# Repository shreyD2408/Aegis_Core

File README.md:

# Aegis Core RP2350A 

# Overview 

When I decided to make the Aegis Core, I set out to make a clean, professional looking, all-in-one controller board for high end automated turrets and robotic aiming platforms. Typically, projects of this kind involve a clutter of jumper wires, stacked development boards, and external regulator boards, all of which can be affected by electrical noise and poor connections in high-vibration moments.

I designed Aegis Core to solve these challenges head-on. By integrating everything onto a custom 2-Layer PCB powered by the new RP2350A, Aegis Core handles real-time USB tracking telemetry, high-current low-side N-Channel MOSFET flywheel driver stages, multi-channel precision servo actuation, automated reloading sequences, and system audio feedback, all driven natively from a compact 2S Li-ion battery architecture.

# How It Works: System Architecture

Aegis Core is structured into three primary electrical and computational domains to ensure high performance and zero brownouts under heavy mechanical load.

1. Power Regulation & Destribution
    Input Stage: Power is connected through an XT30 connector (+BATT) directly connected to a bulk filtering electrolytic capacitor where the severe    inductive current transients that occur when the flywheel motors and servos snap into action are absorbed.
  
  Buck Regulation: A high-efficiency, 500kHz synchronous buck converter reduces the battery voltage range of approximately 7.4V nominal/8.4V max to   a strong and clean 5.0V system rail. Input voltage allows for up to 8S batteries to be connected, although it is not    recommend. Input voltage ranges from 6-30V. The input ceramic decoupling capacitors, output bypass capacitors, bootstrap capacitor and soft-start capacitor are carefully chosen low-ESR surface-mount devices to ensure loop stability. 

2. Processing & Core Logic
   The RP2350 microcontroller is located near the center of the board and is supported by the external Winbond SPI Flash memory, and a 3225-package    crystal oscillator with high precision.

   The RP2350A processes incoming USB serial tracking commands from a host computer running computer vision scripts, translating coordinates into
   smooth PWM signals and hardware triggers in real-time.

3. Actuation & Peripherals
   Flywheel Control: Flywheel cages are driven by a pair of high-current brushed motors controlled by a low-side A03400A N-Channel MOSFET high speed
   electronic switch.

   Servos: Three exclusive header channels for accurate PWM output of 50Hz for pan, tilt, and an automatic reload indexing mechanism.

   Audio & Input: An integrated piezo buzzer emits audible telemetry signals (startup melodies, arming tones and firing clicks), and the tactile
   push buttons allow the user with BOOTSEL and RESET buttons.

# Visuals & Layouts

   Schemaitc:

   Board Layout:

   3D Model:

# Wiring & Interconnect Diagram

Because Aegis Core concentrates peripheral connections onto organized onboard headers, external hand-wiring is kept to an absolute minimum:

- XT30 Connector: Main 2S Li-ion battery input
- Flywheel Output Terminals: Screw terminals connected to the drain pins of the A03400A MOSFET low-side drivers.
- Pan Servo Header: 3-pin header (signal to RP2350 GPIO 0, 5V, GND)
- Tilt Servo Header: 3-pin header (signal to RP2350 GPIO 1, 5V, GND)
- Reload Servo Header: 3 pin header (signal to RP2350 GPIO 2, 5V, GND)
- RGB LED Strip Input: 01x04 Screw Terminal (GPIO 26, 27, 28, 5V). Built for common anode strips.

# BOM

| Part / Description | Notes / Function | Qty | Unit Price | Total Price | Vendor |
| :--- | :--- | :---: | :---: | :---: | :---: |
| Electrolytic Capacitor 220uF | Electrical Noise Filtering | 10 | $0.04 | $0.40 | LCSC |
| Ceramic Capacitor 4.7uF | Passive | 10 | $0.02 | $0.20 | LCSC |
| Ceramic Capacitor 22pF | Passive | 50 | $0.01 | $0.50 | LCSC |
| Ceramic Capacitor 22uF | Passive | 20 | $0.02 | $0.40 | LCSC |
| 1N5819 Diode | Passive | 20 | $0.04 | $0.80 | LCSC |
| XT30 Power Connector | 2S Lithium Battery Input | 5 | $0.23 | $1.15 | LCSC |
| 01x02 Terminal Block | Motor Input | 5 | $0.10 | $0.50 | LCSC |
| Inductor 15uH | Step Down Regulator (Passive) | 5 | $0.10 | $0.50 | LCSC |
| AO3400A N-Channel Mosfet | One-Way Motor Control | 20 | $0.04 | $0.80 | LCSC |
| Resistor 33 Ohms (100 Pack) | Passive | 1 | $0.17 | $0.17 | LCSC |
| Resistor 100K Ohms (100 Pack) | Passive | 1 | $0.21 | $0.21 | LCSC |
| Resistor 100 Ohms (100 Pack) | Passive | 1 | $0.16 | $0.16 | LCSC |
| Resistor 52.3K Ohms (100 Pack) | Passive | 1 | $0.17 | $0.17 | LCSC |
| RP2350A | Raspberry Pi Microcontroller - Brain of the board | 1 | $1.30 | $1.30 | LCSC |
| W25Q128JVSIQ 128MBit Flash Memory | Flash Memory for RP2350A | 1 | $2.80 | $2.80 | LCSC |
| TPS62933DRLR Step Down IC | Voltage Step Down IC | 1 | $0.48 | $0.48 | LCSC |
| Crystal 12MHz | Passive | 5 | $0.09 | $0.45 | LCSC |
| PCB (5 pcs) | Main Board to assemble components on | 1 | $4.00 | $4.00 | JLCPCB |
| Tax & shipping | For the whole order | -- | -- | -- | -- |

# Flashing the Firmware

Download and install the MicroPython Firmware. Download and install the MicroPython Firmware.
Go to the official MicroPython downloads page or the RP2350 port repository to download the latest stable RP2350 .uf2 firmware.

Save the .uf2 file to your computer.

To put Aegis Core in BOOTSEL Mode, follow the steps below.
Find BOOT button (SW1) and RESET button (SW2) on your Aegis Core board.

Press and hold the BOOT button on the Aegis Core, then connect the Aegis Core board to your computer using the USB-C port, and hold the BOOT button down.

Press the BOOT button and then release it. A chime will sound and your computer will identify the board as a virtual USB mass storage device (RPI-RP2 or RP2350).

This step requires flashing the firmware.Step 3: Flash Firmware.
Copy the downloaded MicroPython .uf2 file to the virtual drive window.

The file will now be automatically copied, the board will restart and exit BOOTSEL mode.

Select Step 4: Verify Connection from the pop-up menu.From the pop-up window, choose Step 4: Verify Connection.
Download and open Thonny.

Click on Tools > Options... and then the Interpreter tab.

Select MicroPython (Raspberry Pi Pico) as the interpreter and ensure that the correct USB COM port for Aegis Core is selected. Click OK.

Confirm that the MicroPython interactive prompt (>>>) is on by checking the Shell window below.

Click "step 5" to upload the main.py Control Script.Click step 5 to upload the main.py Control Script.
In Thonny, create a new file, and paste your control script into it, then select File > Save As... > MicroPython device.

Save it to the root directory as file main.py.

Click on the Aegis Core hardware RESET button. The start-up tone should be heard through the buzzer (BZ1) and the console shall print out initialisation logs.

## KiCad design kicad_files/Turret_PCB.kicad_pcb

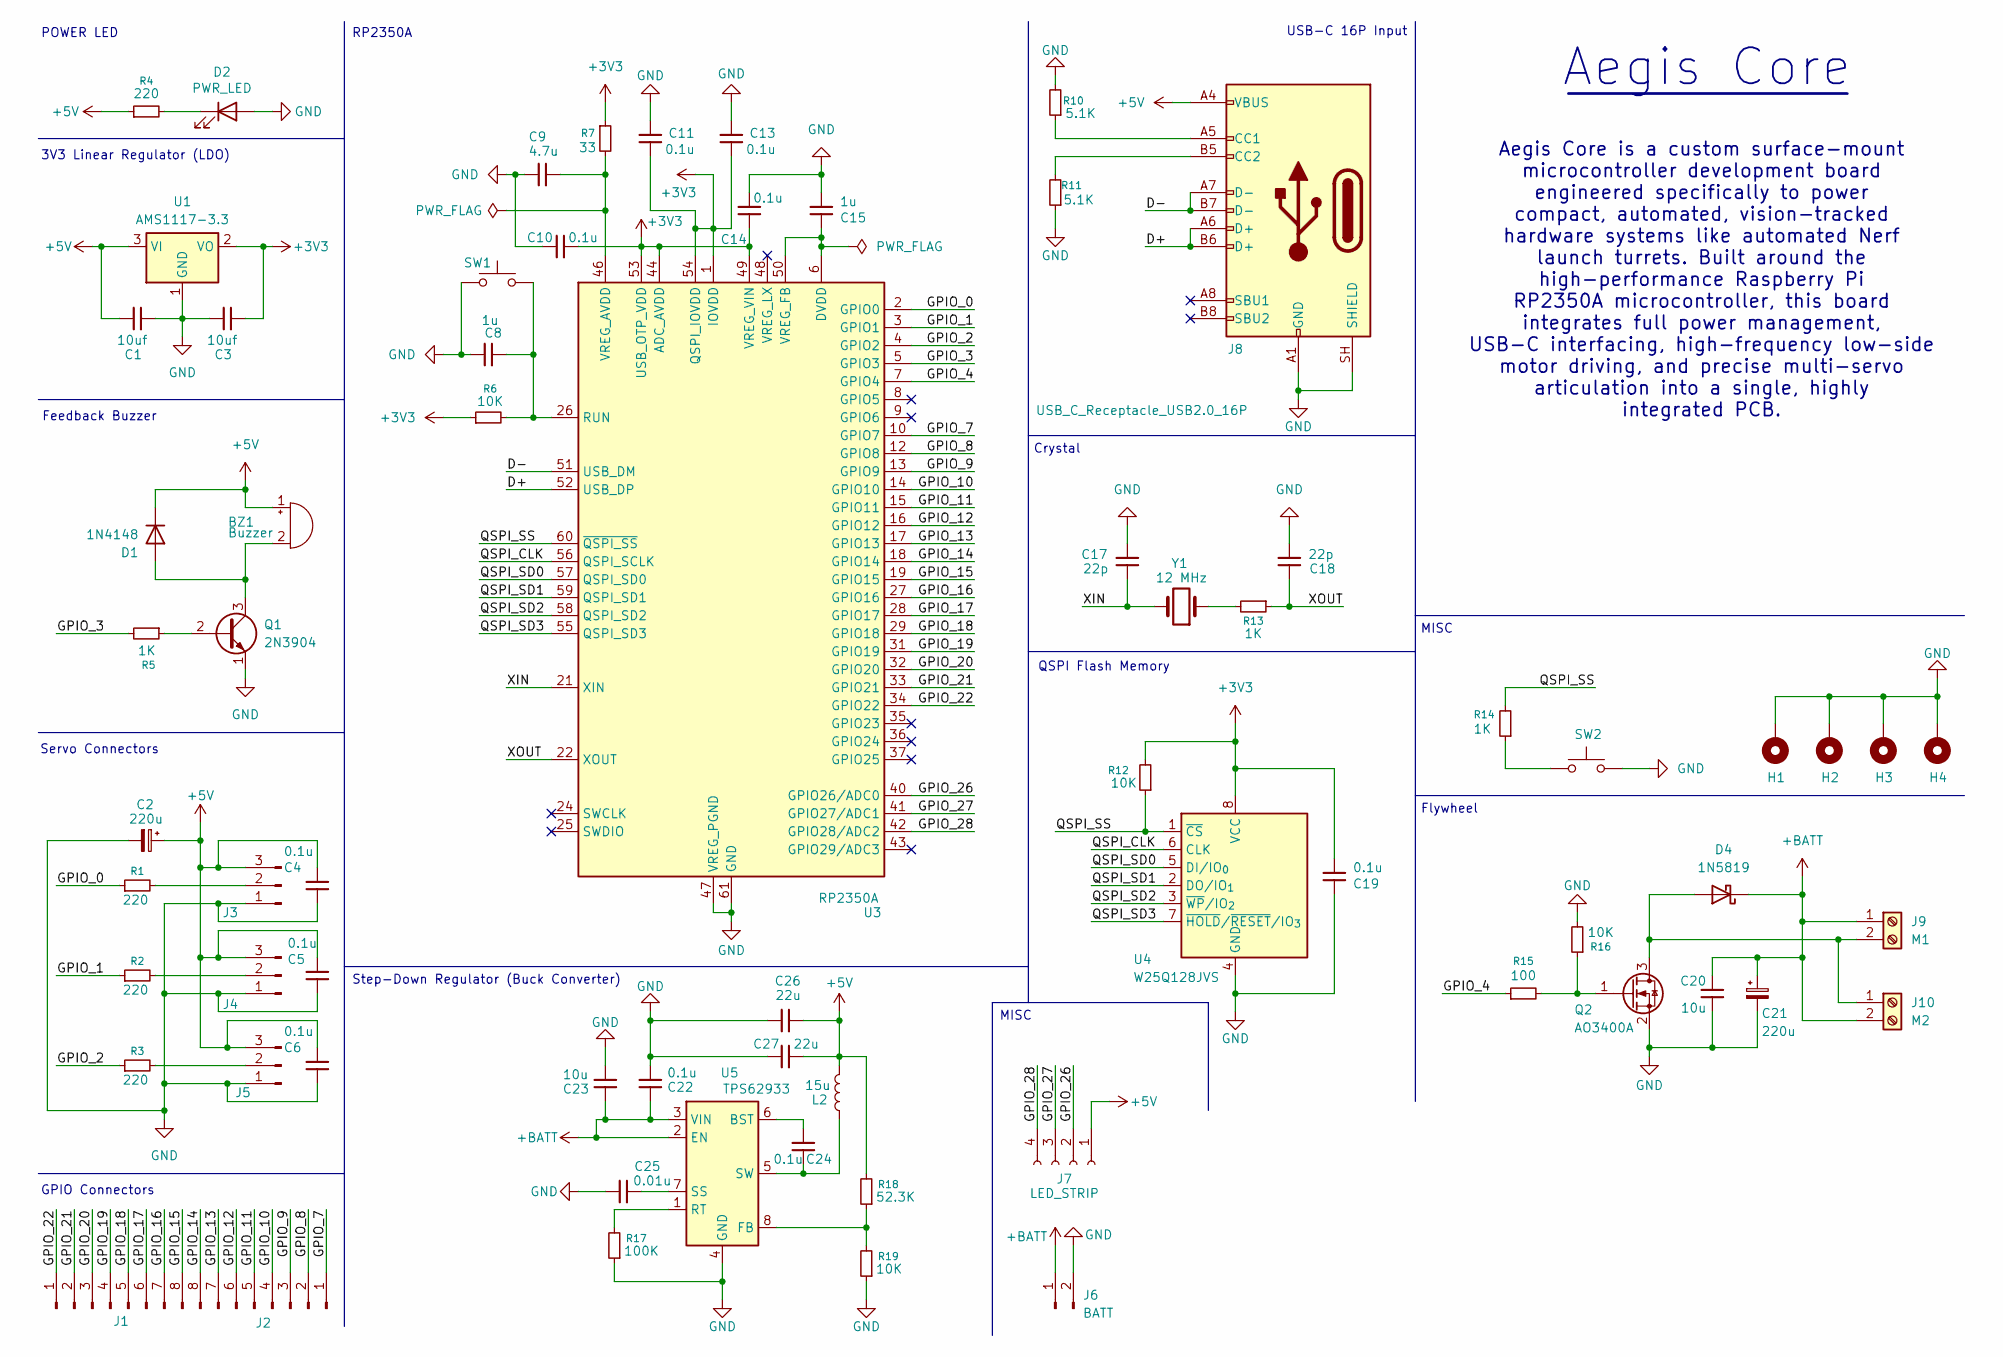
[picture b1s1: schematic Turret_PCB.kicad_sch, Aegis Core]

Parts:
BZ1: Buzzer; Buzzer_12x9.5RM7.6
C1, C3: 10uf; C_0402_1005Metric_Pad0.74x0.62mm_HandSolder
C2, C21: 220u; CP_Elec_6.3x5.4
C4, C5, C6, C10, C11, C13, C14, C19, C22, C24: 0.1u; C_0402_1005Metric_Pad0.74x0.62mm_HandSolder
C8, C15: 1u; C_0402_1005Metric_Pad0.74x0.62mm_HandSolder
C9: 4.7u; C_0402_1005Metric_Pad0.74x0.62mm_HandSolder
C17, C18: 22p; C_0402_1005Metric_Pad0.74x0.62mm_HandSolder
C20, C23: 10u; C_0402_1005Metric_Pad0.74x0.62mm_HandSolder
C25: 0.01u; C_0402_1005Metric_Pad0.74x0.62mm_HandSolder
C26, C27: 22u; C_0402_1005Metric_Pad0.74x0.62mm_HandSolder
D1: 1N4148; D_DO-35_SOD27_P7.62mm_Horizontal
D2: PWR_LED; LED_0402_1005Metric_Pad0.77x0.64mm_HandSolder
D4: 1N5819; D_DO-41_SOD81_P10.16mm_Horizontal
H1, H2, H3, H4: MountingHole_Pad; MountingHole_3.2mm_M3_Pad
J1, J2: Conn_01x08_Pin; PinHeader_1x08_P2.54mm_Vertical
J3, J4, J5: Conn_01x03_Pin; PinHeader_1x03_P2.54mm_Vertical
J6: BATT; AMASS_XT30U-M_1x02_P5.0mm_Vertical
J7: LED_STRIP; TerminalBlock_4Ucon_1x04_P3.50mm_Horizontal
J8: USB_C_Receptacle_USB2.0_16P; USB_C_Receptacle_HCTL_HC-TYPE-C-16P-01A
J9: M1; TerminalBlock_4Ucon_1x02_P3.50mm_Vertical
J10: M2; TerminalBlock_4Ucon_1x02_P3.50mm_Vertical
L2: 15u; L_7.3x7.3_H4.5
Q1: 2N3904; TO-92_Inline
Q2: AO3400A; SOT-23
R1, R2, R3, R4: 220; R_0402_1005Metric_Pad0.72x0.64mm_HandSolder
R5, R13, R14: 1K; R_0402_1005Metric_Pad0.72x0.64mm_HandSolder
R6, R12, R16, R19: 10K; R_0402_1005Metric_Pad0.72x0.64mm_HandSolder
R7: 33; R_0402_1005Metric_Pad0.72x0.64mm_HandSolder
R10, R11: 5.1K; R_0402_1005Metric_Pad0.72x0.64mm_HandSolder
R15: 100; R_0402_1005Metric_Pad0.72x0.64mm_HandSolder
R17: 100K; R_0402_1005Metric_Pad0.72x0.64mm_HandSolder
R18: 52.3K; R_0402_1005Metric_Pad0.72x0.64mm_HandSolder
SW1, SW2: SW_Push; SW_SPST_EVQP2_ShortPushTravel_H2.1mm
U1: AMS1117-3.3; SOT-223-3_TabPin2
U3: RP2350A; QFN-60-1EP_7x7mm_P0.4mm_EP3.4x3.4mm_ThermalVias
U4: W25Q128JVS; SOIC-8_3.9x4.9mm_P1.27mm
U5: TPS62933; SOT-583-8
Y1: 12 MHz; Crystal_SMD_5032-2Pin_5.0x3.2mm_HandSoldering

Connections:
+3V3: C3.2, C10.1, C11.1, C13.1, C14.1, C19.1, R6.1, R7.1, R12.2, U1.2 (VO), U3.1 (IOVDD), U3.11 (IOVDD), U3.20 (IOVDD), U3.30 (IOVDD), U3.38 (IOVDD), U3.44 (ADC_AVDD), U3.45 (IOVDD), U3.49 (VREG_VIN), U3.53 (USB_OTP_VDD), U3.54 (QSPI_IOVDD), U4.8 (VCC)
+5V: BZ1.1 (+), C1.1, C2.1, C4.1, C5.1, C6.1, C26.2, C27.2, D1.1 (K), J3.3, J4.3, J5.3, J7.1, J8.A4 (VBUS), J8.A9 (VBUS), J8.B4 (VBUS), J8.B9 (VBUS), L2.2, R4.1, R18.2, U1.3 (VI)
+BATT: C20.2, C21.1, C22.2, C23.2, D4.1 (K), J6.1, J9.1, J10.2, U5.2 (EN), U5.3 (VIN)
/D+: J8.A6 (D+), J8.B6 (D+), U3.52 (USB_DP)
/D-: J8.A7 (D-), J8.B7 (D-), U3.51 (USB_DM)
/GPIO_0: R1.1, U3.2 (GPIO0)
/GPIO_1: R2.1, U3.3 (GPIO1)
/GPIO_2: R3.1, U3.4 (GPIO2)
/GPIO_3: R5.2, U3.5 (GPIO3)
/GPIO_4: R15.1, U3.7 (GPIO4)
/GPIO_7: J2.1, U3.10 (GPIO7)
/GPIO_8: J2.2, U3.12 (GPIO8)
/GPIO_9: J2.3, U3.13 (GPIO9)
/GPIO_10: J2.4, U3.14 (GPIO10)
/GPIO_11: J2.5, U3.15 (GPIO11)
/GPIO_12: J2.6, U3.16 (GPIO12)
/GPIO_13: J2.7, U3.17 (GPIO13)
/GPIO_14: J2.8, U3.18 (GPIO14)
/GPIO_15: J1.8, U3.19 (GPIO15)
/GPIO_16: J1.7, U3.27 (GPIO16)
/GPIO_17: J1.6, U3.28 (GPIO17)
/GPIO_18: J1.5, U3.29 (GPIO18)
/GPIO_19: J1.4, U3.31 (GPIO19)
/GPIO_20: J1.3, U3.32 (GPIO20)
/GPIO_21: J1.2, U3.33 (GPIO21)
/GPIO_22: J1.1, U3.34 (GPIO22)
/GPIO_26: J7.2, U3.40 (GPIO26/ADC0)
/GPIO_27: J7.3, U3.41 (GPIO27/ADC1)
/GPIO_28: J7.4, U3.42 (GPIO28/ADC2)
/QSPI_CLK: U3.56 (QSPI_SCLK), U4.6 (CLK)
/QSPI_SD0: U3.57 (QSPI_SD0), U4.5 (DI/IO_{0})
/QSPI_SD1: U3.59 (QSPI_SD1), U4.2 (DO/IO_{1})
/QSPI_SD2: U3.58 (QSPI_SD2), U4.3 (~WP/IO_{2})
/QSPI_SD3: U3.55 (QSPI_SD3), U4.7 (~HOLD/~RESET/IO_{3})
/QSPI_SS: R12.1, R14.2, U3.60 (~QSPI_SS), U4.1 (~CS)
/XIN: C17.2, U3.21 (XIN), Y1.2
/XOUT: C18.1, R13.1, U3.22 (XOUT)
GND: C1.2, C2.2, C3.1, C4.2, C5.2, C6.2, C8.1, C9.2, C10.2, C11.2, C13.2, C14.2, C15.1, C17.1, C18.2, C19.2, C20.1, C21.2, C22.1, C23.1, C25.1, C26.1, C27.1, D2.2 (A), H1.1 (1_1), H2.1 (1_1), H3.1 (1_1), H4.1 (1_1), J3.1, J4.1, J5.1, J6.2, J8.A1 (GND), J8.A12 (GND), J8.B1 (GND), J8.B12 (GND), J8.SH (SHIELD), Q1.1 (E), Q2.2 (S), R10.2, R11.1, R16.2, R17.1, R19.1, SW1.1, SW2.2, U1.1 (GND), U3.47 (VREG_PGND), U3.61 (GND), U4.4 (GND), U5.4 (GND)
unnamed: BZ1.2 (-), D1.2 (A), Q1.3 (C)
unnamed: D2.1 (K), R4.2
unnamed: D4.2 (A), J9.2, J10.1, Q2.3 (D)
unnamed: J3.2, R1.2
unnamed: J4.2, R2.2
unnamed: J5.2, R3.2
unnamed: J8.A5 (CC1), R10.1
unnamed: J8.B5 (CC2), R11.2
unnamed: Q1.2 (B), R5.1
unnamed: Q2.1 (G), R15.2, R16.1
unnamed: R13.2, Y1.1
unnamed: R14.1, SW2.1
unnamed: C8.2, R6.2, SW1.2, U3.26 (RUN)
unnamed: C9.1, R7.2, U3.46 (VREG_AVDD)
unnamed: C15.2, U3.6 (DVDD), U3.23 (DVDD), U3.39 (DVDD), U3.50 (VREG_FB)
unnamed: C24.1, U5.6 (BST)
unnamed: R18.1, R19.2, U5.8 (FB)
unnamed: R17.2, U5.1 (RT)
unnamed: C25.2, U5.7 (SS)
unnamed: C24.2, L2.1, U5.5 (SW)

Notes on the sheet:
Crystal
Feedback Buzzer
RP2350A
MISC
QSPI Flash Memory
Servo Connectors
USB-C 16P Input
Flywheel
Step-Down Regulator (Buck Converter)
Aegis Core is a custom surface-mount microcontroller development board engineered specifically to power compact, automated, vision-tracked hardware systems like automated Nerf launch turrets. Built around the high-performance Raspberry Pi RP2350A microcontroller, this board integrates full power ma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
GPIO Connectors
POWER LED
Aegis Core
3V3 Linear Regulator (LDO)

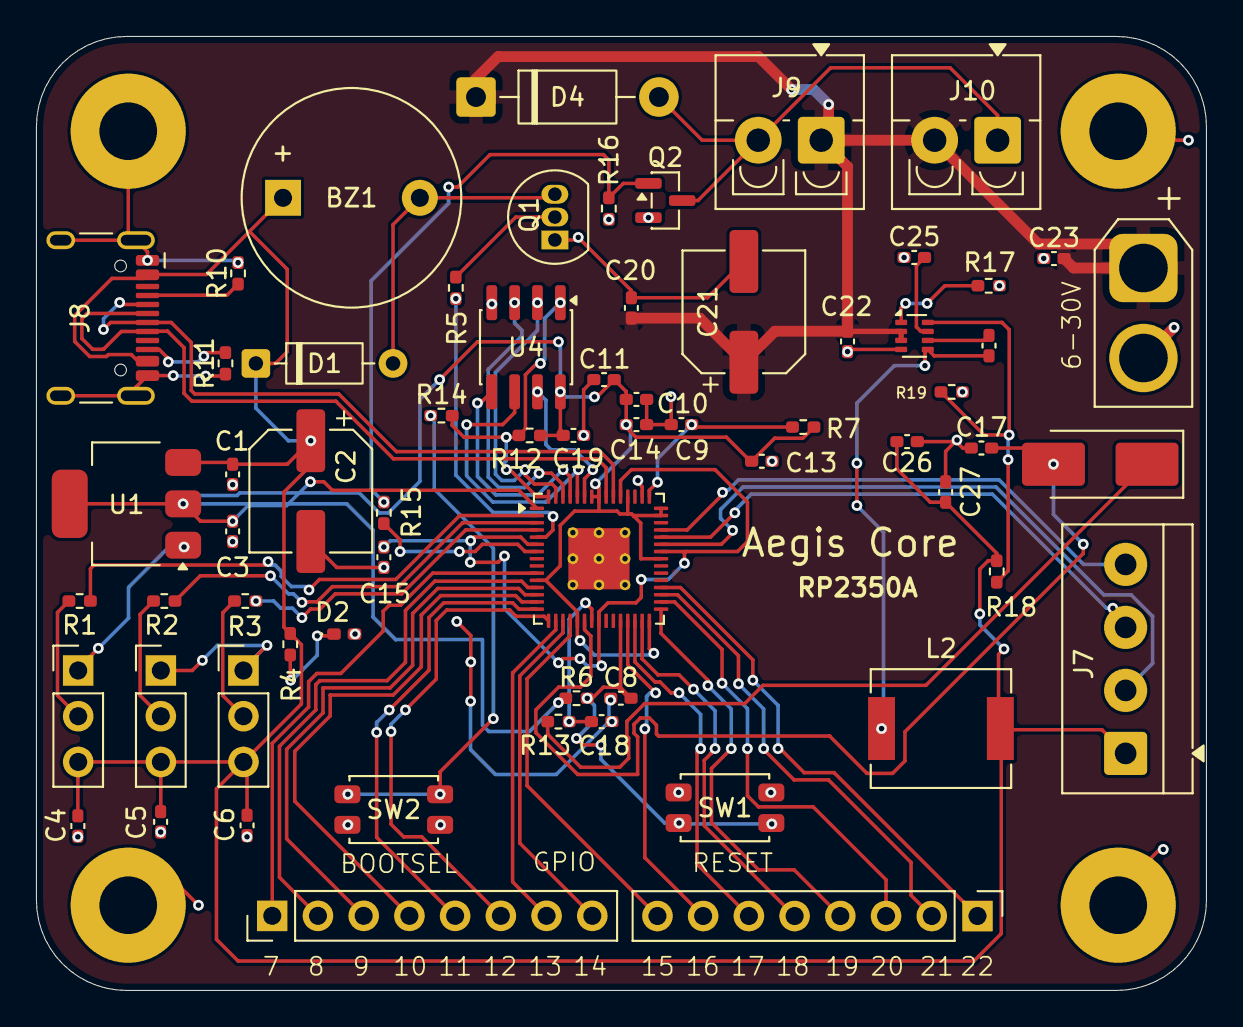
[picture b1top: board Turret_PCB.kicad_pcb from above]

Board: 2 copper layers, 65.0 x 53.0 mm, 69 parts (0 on the bottom side), 58 nets.
